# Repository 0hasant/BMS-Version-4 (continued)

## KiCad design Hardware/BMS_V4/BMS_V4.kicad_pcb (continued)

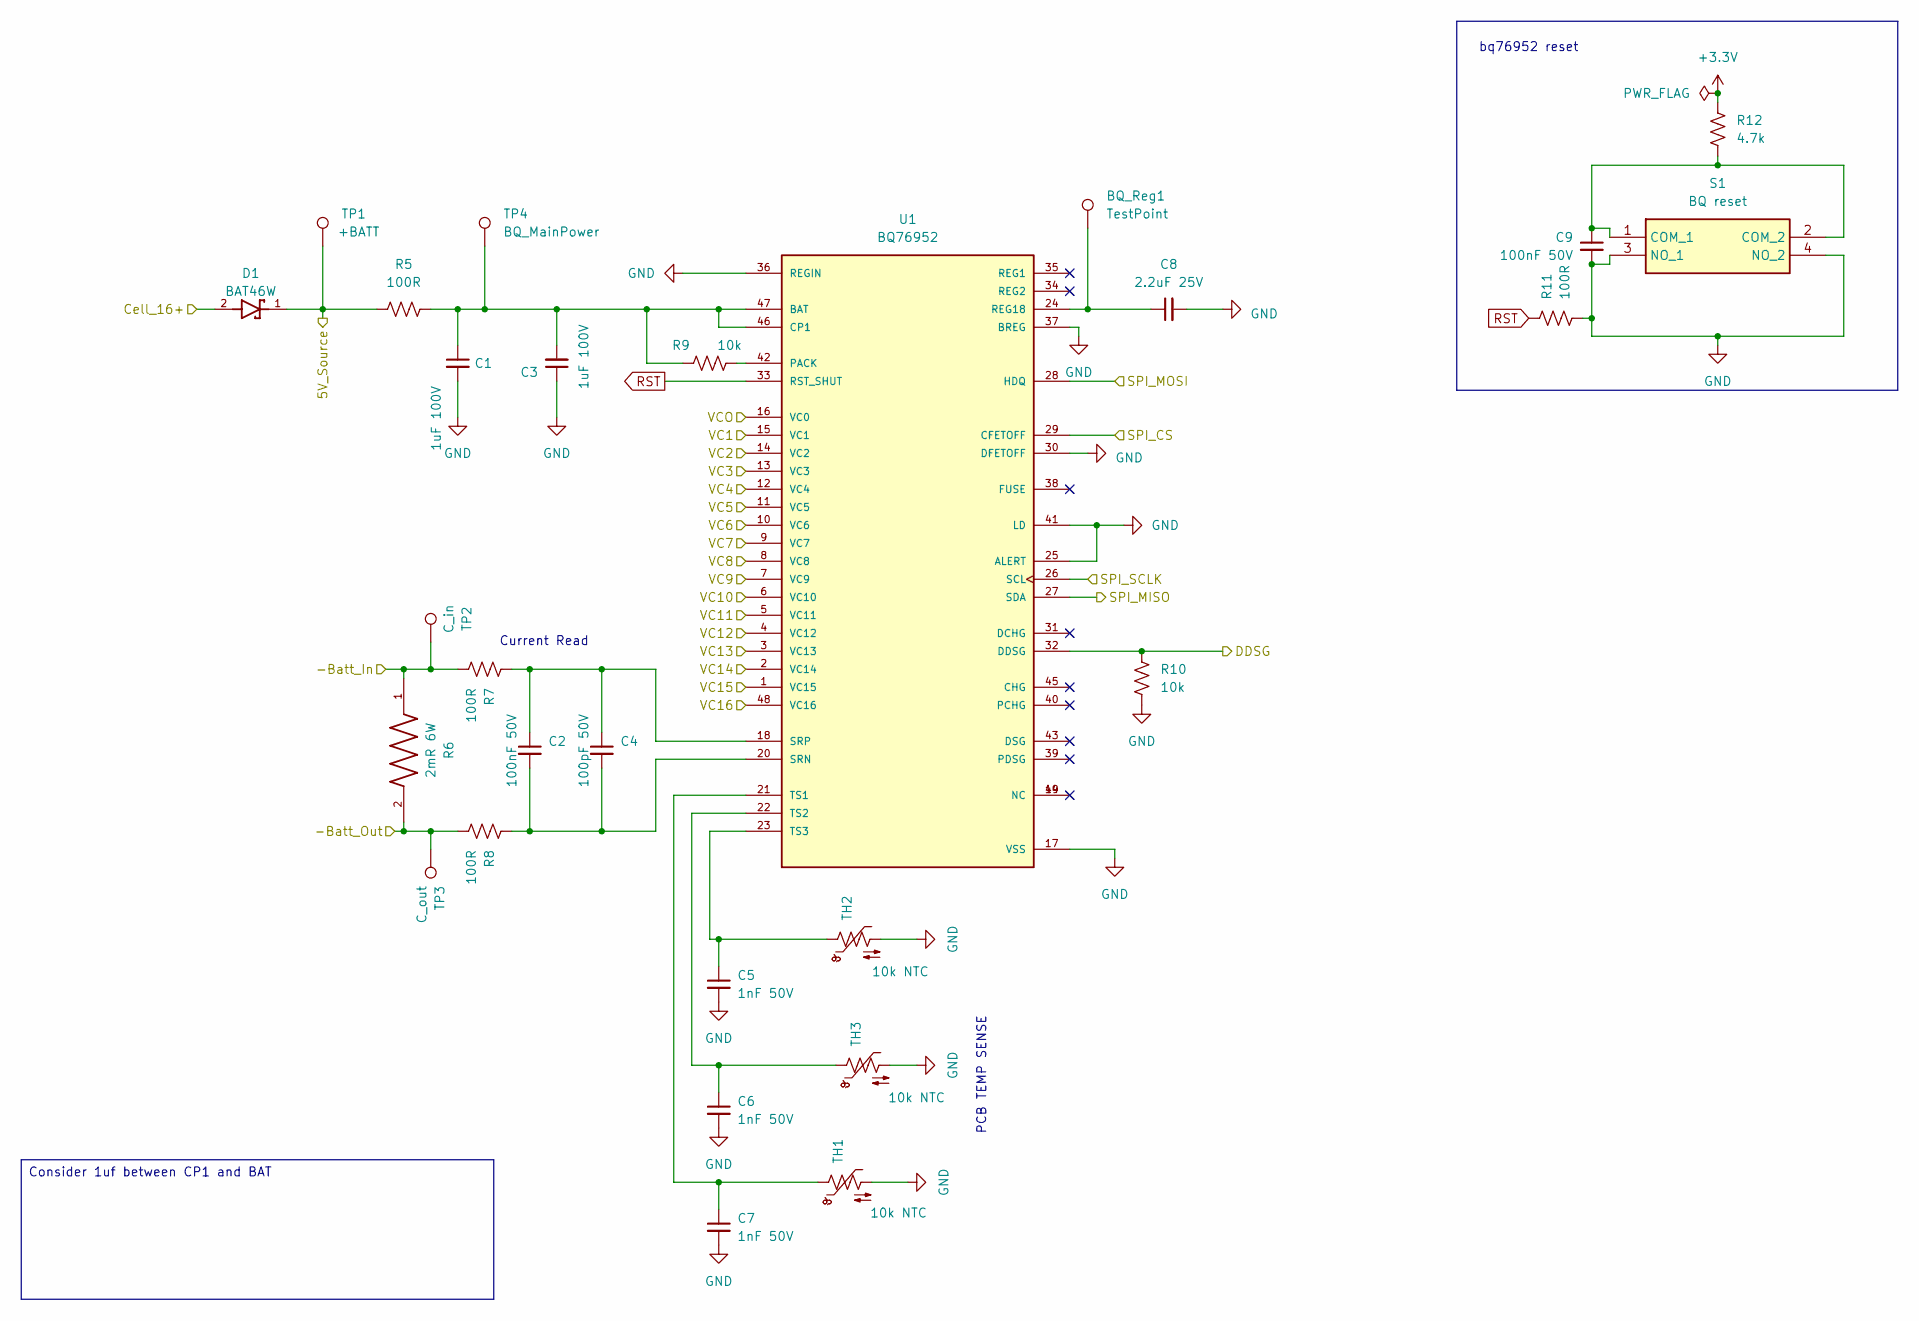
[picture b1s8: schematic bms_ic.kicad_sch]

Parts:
BQ_Reg1: TestPoint; Pin_D0.7mm_L6.5mm_W1.8mm_FlatFork
C1: 1uF 100V; C_1206_3216Metric_Pad1.33x1.80mm_HandSolder; MPN CL31B105KCHNNNE
C2, C9: 100nF 50V; C_0805_2012Metric_Pad1.18x1.45mm_HandSolder; MPN CL21B104KBCNNNC
C3: 1uF 100V; C_0805_2012Metric_Pad1.18x1.45mm_HandSolder; MPN CL21Y105KCFVPJE
C4: 100pF 50V; C_0805_2012Metric_Pad1.18x1.45mm_HandSolder; MPN CL21C101JBANNNC
C5, C6, C7: 1nF 50V; C_0805_2012Metric_Pad1.18x1.45mm_HandSolder; MPN MCF05KTB500102
C8: 2.2uF 25V; C_0805_2012Metric_Pad1.18x1.45mm_HandSolder; MPN CL21B225KAFNNNE
D1: BAT46W; SOD3715X145N; MPN BAT46W-7-F
R5, R11: 100R; R_0805_2012Metric_Pad1.20x1.40mm_HandSolder; MPN 0805S8F1000T5E
R6: 2mR 6W; RESC10052X125N; MPN BVS-A-R002-1.0
R7, R8: 100R; RES_ERA6AHD330V; MPN 0805S8F1000T5E
R9, R10: 10k; R_0805_2012Metric_Pad1.20x1.40mm_HandSolder; MPN 0805S8J0103T5E
R12: 4.7k; R_0805_2012Metric_Pad1.20x1.40mm_HandSolder; MPN CRT05F7E4701
S1: BQ reset; DTS62RV; MPN DTS-62R-V; Mouser Part Number 113-DTS62RV
TH1, TH2, TH3: 10k NTC; R_0805_2012Metric_Pad1.20x1.40mm_HandSolder; MPN TSM2A103F3951RZ
TP1: +BATT; TestPoint_THTPad_D1.0mm_Drill0.5mm
TP2: C_in; TestPoint_THTPad_D1.0mm_Drill0.5mm
TP3: C_out; TestPoint_THTPad_D1.0mm_Drill0.5mm
TP4: BQ_MainPower; TestPoint_THTPad_D1.0mm_Drill0.5mm
U1: BQ76952; QFP50P900X900X120-48N; MPN BQ76952PFBR

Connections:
+3.3V: R12.1; also elsewhere on the board
/Additional Circuits/Cont_PhotoMOS_Anode: R10.2, U1.32 (DDSG); also elsewhere on the board
/BMS_IC/5V_Source: D1.1, R5.1, TP1.1 (1_1); also elsewhere on the board
/BMS_IC/-Batt_In: R6.1, R7.2, TP2.1 (1_1); also elsewhere on the board
/BMS_IC/-Batt_Out: R6.2, R8.2, TP3.1 (1_1); also elsewhere on the board
/BMS_IC/SPI_CS: U1.29 (CFETOFF); also elsewhere on the board
/BMS_IC/SPI_MISO: U1.27 (SDA); also elsewhere on the board
/BMS_IC/SPI_MOSI: U1.28 (HDQ); also elsewhere on the board
/BMS_IC/SPI_SCLK: U1.26 (SCL); also elsewhere on the board
/BMS_IC/VC1: U1.15 (VC1); also elsewhere on the board
/BMS_IC/VC2: U1.14 (VC2); also elsewhere on the board
/BMS_IC/VC3: U1.13 (VC3); also elsewhere on the board
/BMS_IC/VC4: U1.12 (VC4); also elsewhere on the board
/BMS_IC/VC5: U1.11 (VC5); also elsewhere on the board
/BMS_IC/VC6: U1.10 (VC6); also elsewhere on the board
/BMS_IC/VC7: U1.9 (VC7); also elsewhere on the board
/BMS_IC/VC8: U1.8 (VC8); also elsewhere on the board
/BMS_IC/VC9: U1.7 (VC9); also elsewhere on the board
/BMS_IC/VC10: U1.6 (VC10); also elsewhere on the board
/BMS_IC/VC11: U1.5 (VC11); also elsewhere on the board
/BMS_IC/VC12: U1.4 (VC12); also elsewhere on the board
/BMS_IC/VC13: U1.3 (VC13); also elsewhere on the board
/BMS_IC/VC14: U1.2 (VC14); also elsewhere on the board
/BMS_IC/VC15: U1.1 (VC15); also elsewhere on the board
/BMS_IC/VC16: U1.48 (VC16); also elsewhere on the board
/BMS_IC/VCO: U1.16 (VC0); also elsewhere on the board
Cell16+: D1.2; also elsewhere on the board
GND: C1.2, C3.1, C5.2, C6.2, C7.2, C8.2, C9.2, R10.1, R11.1, S1.3 (NO_1), S1.4 (NO_2), TH1.2, TH2.2, TH3.2, U1.17 (VSS), U1.25 (ALERT), U1.30 (DFETOFF), U1.36 (REGIN), U1.37 (BREG), U1.41 (LD); also elsewhere on the board
unnamed: C9.1, R12.2, S1.1 (COM_1), S1.2 (COM_2)
unnamed: C1.1, C3.2, R5.2, R9.1, TP4.1 (1_1), U1.46 (CP1), U1.47 (BAT)
unnamed: R9.2, U1.42 (PACK)
unnamed 156: BQ_Reg1.1, C8.1, U1.24 (REG18); also elsewhere on the board
unnamed: C2.2, C4.2, R8.1, U1.20 (SRN)
unnamed: C2.1, C4.1, R7.1, U1.18 (SRP)
unnamed: C7.1, TH1.1, U1.21 (TS1)
unnamed: C6.1, TH3.1, U1.22 (TS2)
unnamed: C5.1, TH2.1, U1.23 (TS3)
RST: R11.2, U1.33 (RST_SHUT)

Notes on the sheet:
Current Read
PCB TEMP SENSE
bq76952 reset
Consider 1uf between CP1 and BAT

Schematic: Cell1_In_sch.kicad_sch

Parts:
C40, C41: 220nF 50V; C_0805_2012Metric; MPN CL21B224KBFNNNE
D6: BZX584C4V7; D_SOD-523; MPN BZX584C4V7_R2_00001
D7: LED red; LED_0805_2012Metric_Pad1.15x1.40mm_HandSolder; MPN HL-PSC-2012S9AC
Q2: SI1050X; SOTFL50P160X60-6N; MPN SI1050X-T1-GE3
R39: 1k; R_0805_2012Metric_Pad1.20x1.40mm_HandSolder; MPN 0805S8F1001T5E
R40, R41: 100R; R_0805_2012Metric_Pad1.20x1.40mm_HandSolder; MPN CRT05F7E1000
R42: 22R 2W; R_2512_6332Metric_Pad1.40x3.35mm_HandSolder; MPN HP122WJ0220T4E
R43: 0R; R_0805_2012Metric_Pad1.20x1.40mm_HandSolder; MPN 0805S8F0000TDE
R44: 470R; R_0805_2012Metric_Pad1.20x1.40mm_HandSolder; MPN 0805S8F4700T5E
TP10: GND_Test; TestPoint_THTPad_1.5x1.5mm_Drill0.7mm

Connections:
/BMS_IC/VC1: C40.1, R41.1; also elsewhere on the board
/BMS_IC/VCO: C41.1, R39.1, R40.1; also elsewhere on the board
/CellBalance_Input/Cell0: D6.2 (A), Q2.4 (S), R40.2, R43.1; also elsewhere on the board
/CellBalance_Input/Cell1: D7.2 (A), R41.2, R42.1; also elsewhere on the board
GND: C40.2, C41.2, R43.2, TP10.1; also elsewhere on the board
unnamed: D6.1 (K), Q2.3 (G), R39.2
unnamed: D7.1 (K), R44.1
unnamed: Q2.1 (D), Q2.2 (D), Q2.5 (D), Q2.6 (D), R42.2, R44.2

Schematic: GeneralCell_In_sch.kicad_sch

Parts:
C39: 220nF 50V; C_0805_2012Metric; MPN CL21B224KBFNNNE
D4: BZX584C4V7; D_SOD-523; MPN BZX584C4V7_R2_00001
D5: LED red; LED_0805_2012Metric_Pad1.15x1.40mm_HandSolder; MPN HL-PSC-2012S9AC
Q1: SI1050X; SOTFL50P160X60-6N; MPN SI1050X-T1-GE3
R35: 100R; R_0805_2012Metric_Pad1.20x1.40mm_HandSolder; MPN CRT05F7E1000
R36: 1k; R_0805_2012Metric_Pad1.20x1.40mm_HandSolder; MPN 0805S8F1001T5E
R37: 22R 2W; R_2512_6332Metric_Pad1.40x3.35mm_HandSolder; MPN HP122WJ0220T4E
R38: 470R; R_0805_2012Metric_Pad1.20x1.40mm_HandSolder; MPN 0805S8F4700T5E

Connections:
/BMS_IC/VC1: C39.2, R36.1; also elsewhere on the board
/BMS_IC/VC2: C39.1, R35.1; also elsewhere on the board
/CellBalance_Input/Cell1: D4.2 (A), Q1.4 (S); also elsewhere on the board
/CellBalance_Input/Cell2: D5.2 (A), R35.2, R37.1; also elsewhere on the board
unnamed: D4.1 (K), Q1.3 (G), R36.2
unnamed: D5.1 (K), R38.1
unnamed: Q1.1 (D), Q1.2 (D), Q1.5 (D), Q1.6 (D), R37.2, R38.2

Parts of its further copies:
C42, C43, C44, C45, C46, C47, C48, C49, C50, C51, C52, C53, C54: 220nF 50V; C_0805_2012Metric; MPN CL21B224KBFNNNE
D8, D10, D12, D14, D16, D18, D20, D22, D24, D26, D28, D30, D32: BZX584C4V7; D_SOD-523; MPN BZX584C4V7_R2_00001
D9, D11, D13, D15, D17, D19, D21, D23, D25, D27, D29, D31, D33: LED red; LED_0805_2012Metric_Pad1.15x1.40mm_HandSolder; MPN HL-PSC-2012S9AC
Q3, Q4, Q5, Q6, Q7, Q8, Q9, Q10, Q11, Q12, Q13, Q14, Q15: SI1050X; SOTFL50P160X60-6N; MPN SI1050X-T1-GE3
R45, R49, R53, R57, R61, R65, R69, R73, R77, R81, R85, R89, R93: 100R; R_0805_2012Metric_Pad1.20x1.40mm_HandSolder; MPN CRT05F7E1000
R46, R50, R54, R58, R62, R66, R70, R74, R78, R82, R86, R90, R94: 1k; R_0805_2012Metric_Pad1.20x1.40mm_HandSolder; MPN 0805S8F1001T5E
R47, R51, R55, R59, R63, R67, R71, R75, R79, R83, R87, R91, R95: 22R 2W; R_2512_6332Metric_Pad1.40x3.35mm_HandSolder; MPN HP122WJ0220T4E
R48, R52, R56, R60, R64, R68, R72, R76, R80, R84, R88, R92, R96: 470R; R_0805_2012Metric_Pad1.20x1.40mm_HandSolder; MPN 0805S8F4700T5E

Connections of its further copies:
/BMS_IC/VC2: C42.2, R46.1; also elsewhere on the board
/BMS_IC/VC3: C42.1, C43.2, R45.1, R50.1; also elsewhere on the board
/BMS_IC/VC4: C43.1, C44.2, R49.1, R54.1; also elsewhere on the board
/BMS_IC/VC5: C44.1, C45.2, R53.1, R58.1; also elsewhere on the board
/BMS_IC/VC6: C45.1, C46.2, R57.1, R62.1; also elsewhere on the board
/BMS_IC/VC7: C46.1, C47.2, R61.1, R66.1; also elsewhere on the board
/BMS_IC/VC8: C47.1, C48.2, R65.1, R70.1; also elsewhere on the board
/BMS_IC/VC9: C48.1, C49.2, R69.1, R74.1; also elsewhere on the board
/BMS_IC/VC10: C49.1, C50.2, R73.1, R78.1; also elsewhere on the board
/BMS_IC/VC11: C50.1, C51.2, R77.1, R82.1; also elsewhere on the board
/BMS_IC/VC12: C51.1, C52.2, R81.1, R86.1; also elsewhere on the board
/BMS_IC/VC13: C52.1, C53.2, R85.1, R90.1; also elsewhere on the board
/BMS_IC/VC14: C53.1, C54.2, R89.1, R94.1; also elsewhere on the board
/BMS_IC/VC15: C54.1, R93.1; also elsewhere on the board
/CellBalance_Input/Cell2: D8.2 (A), Q3.4 (S); also elsewhere on the board
/CellBalance_Input/Cell3: D9.2 (A), D10.2 (A), Q4.4 (S), R45.2, R47.1; also elsewhere on the board
/CellBalance_Input/Cell4: D11.2 (A), D12.2 (A), Q5.4 (S), R49.2, R51.1; also elsewhere on the board
/CellBalance_Input/Cell5: D13.2 (A), D14.2 (A), Q6.4 (S), R53.2, R55.1; also elsewhere on the board
/CellBalance_Input/Cell6: D15.2 (A), D16.2 (A), Q7.4 (S), R57.2, R59.1; also elsewhere on the board
/CellBalance_Input/Cell7: D17.2 (A), D18.2 (A), Q8.4 (S), R61.2, R63.1; also elsewhere on the board
/CellBalance_Input/Cell8: D19.2 (A), D20.2 (A), Q9.4 (S), R65.2, R67.1; also elsewhere on the board
/CellBalance_Input/Cell9: D21.2 (A), D22.2 (A), Q10.4 (S), R69.2, R71.1; also elsewhere on the board
/CellBalance_Input/Cell10: D23.2 (A), D24.2 (A), Q11.4 (S), R73.2, R75.1; also elsewhere on the board
/CellBalance_Input/Cell11: D25.2 (A), D26.2 (A), Q12.4 (S), R77.2, R79.1; also elsewhere on the board
/CellBalance_Input/Cell12: D27.2 (A), D28.2 (A), Q13.4 (S), R81.2, R83.1; also elsewhere on the board
/CellBalance_Input/Cell13: D29.2 (A), D30.2 (A), Q14.4 (S), R85.2, R87.1; also elsewhere on the board
/CellBalance_Input/Cell14: D31.2 (A), D32.2 (A), Q15.4 (S), R89.2, R91.1; also elsewhere on the board
/CellBalance_Input/Cell15: D33.2 (A), R93.2, R95.1; also elsewhere on the board
unnamed: D8.1 (K), Q3.3 (G), R46.2
unnamed: D9.1 (K), R48.1
unnamed: D10.1 (K), Q4.3 (G), R50.2
unnamed: D11.1 (K), R52.1
unnamed: D12.1 (K), Q5.3 (G), R54.2
unnamed: D13.1 (K), R56.1
unnamed: D14.1 (K), Q6.3 (G), R58.2
unnamed: D15.1 (K), R60.1
unnamed: D16.1 (K), Q7.3 (G), R62.2
unnamed: D17.1 (K), R64.1
unnamed: D18.1 (K), Q8.3 (G), R66.2
unnamed: D19.1 (K), R68.1
unnamed: D20.1 (K), Q9.3 (G), R70.2
unnamed: D21.1 (K), R72.1
unnamed: D22.1 (K), Q10.3 (G), R74.2
unnamed: D23.1 (K), R76.1
unnamed: D24.1 (K), Q11.3 (G), R78.2
unnamed: D25.1 (K), R80.1
unnamed: D26.1 (K), Q12.3 (G), R82.2
unnamed: D27.1 (K), R84.1
unnamed: D28.1 (K), Q13.3 (G), R86.2
unnamed: D29.1 (K), R88.1
unnamed: D30.1 (K), Q14.3 (G), R90.2
unnamed: D31.1 (K), R92.1
unnamed: D32.1 (K), Q15.3 (G), R94.2
unnamed: D33.1 (K), R96.1
unnamed: Q3.1 (D), Q3.2 (D), Q3.5 (D), Q3.6 (D), R47.2, R48.2
unnamed: Q4.1 (D), Q4.2 (D), Q4.5 (D), Q4.6 (D), R51.2, R52.2
unnamed: Q5.1 (D), Q5.2 (D), Q5.5 (D), Q5.6 (D), R55.2, R56.2
unnamed: Q6.1 (D), Q6.2 (D), Q6.5 (D), Q6.6 (D), R59.2, R60.2
unnamed: Q7.1 (D), Q7.2 (D), Q7.5 (D), Q7.6 (D), R63.2, R64.2
unnamed: Q8.1 (D), Q8.2 (D), Q8.5 (D), Q8.6 (D), R67.2, R68.2
unnamed: Q9.1 (D), Q9.2 (D), Q9.5 (D), Q9.6 (D), R71.2, R72.2
unnamed: Q10.1 (D), Q10.2 (D), Q10.5 (D), Q10.6 (D), R75.2, R76.2
unnamed: Q11.1 (D), Q11.2 (D), Q11.5 (D), Q11.6 (D), R79.2, R80.2
unnamed: Q12.1 (D), Q12.2 (D), Q12.5 (D), Q12.6 (D), R83.2, R84.2
unnamed: Q13.1 (D), Q13.2 (D), Q13.5 (D), Q13.6 (D), R87.2, R88.2
unnamed: Q14.1 (D), Q14.2 (D), Q14.5 (D), Q14.6 (D), R91.2, R92.2
unnamed: Q15.1 (D), Q15.2 (D), Q15.5 (D), Q15.6 (D), R95.2, R96.2

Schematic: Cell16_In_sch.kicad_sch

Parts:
C55: 220nF 50V; C_0805_2012Metric; MPN CL21B224KBFNNNE
D34: BZX584C4V7; D_SOD-523; MPN BZX584C4V7_R2_00001
D35: LED red; LED_0805_2012Metric_Pad1.15x1.40mm_HandSolder; MPN HL-PSC-2012S9AC
Q16: SI1050X; SOTFL50P160X60-6N; MPN SI1050X-T1-GE3
R97: 20R; RESC2012X70N; MPN 0805S8F200JT5E
R98: 1k; R_0805_2012Metric_Pad1.20x1.40mm_HandSolder; MPN 0805S8F1001T5E
R99: 22R 2W; R_2512_6332Metric_Pad1.40x3.35mm_HandSolder; MPN HP122WJ0220T4E
R100: 470R; R_0805_2012Metric_Pad1.20x1.40mm_HandSolder; MPN 0805S8F4700T5E

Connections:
/BMS_IC/VC15: C55.2, R98.1; also elsewhere on the board
/BMS_IC/VC16: C55.1, R97.1; also elsewhere on the board
/CellBalance_Input/Cell15: D34.2 (A), Q16.4 (S); also elsewhere on the board
Cell16+: D35.2 (A), R97.2, R99.1; also elsewhere on the board
unnamed: D34.1 (K), Q16.3 (G), R98.2
unnamed: D35.1 (K), R100.1
unnamed: Q16.1 (D), Q16.2 (D), Q16.5 (D), Q16.6 (D), R99.2, R100.2

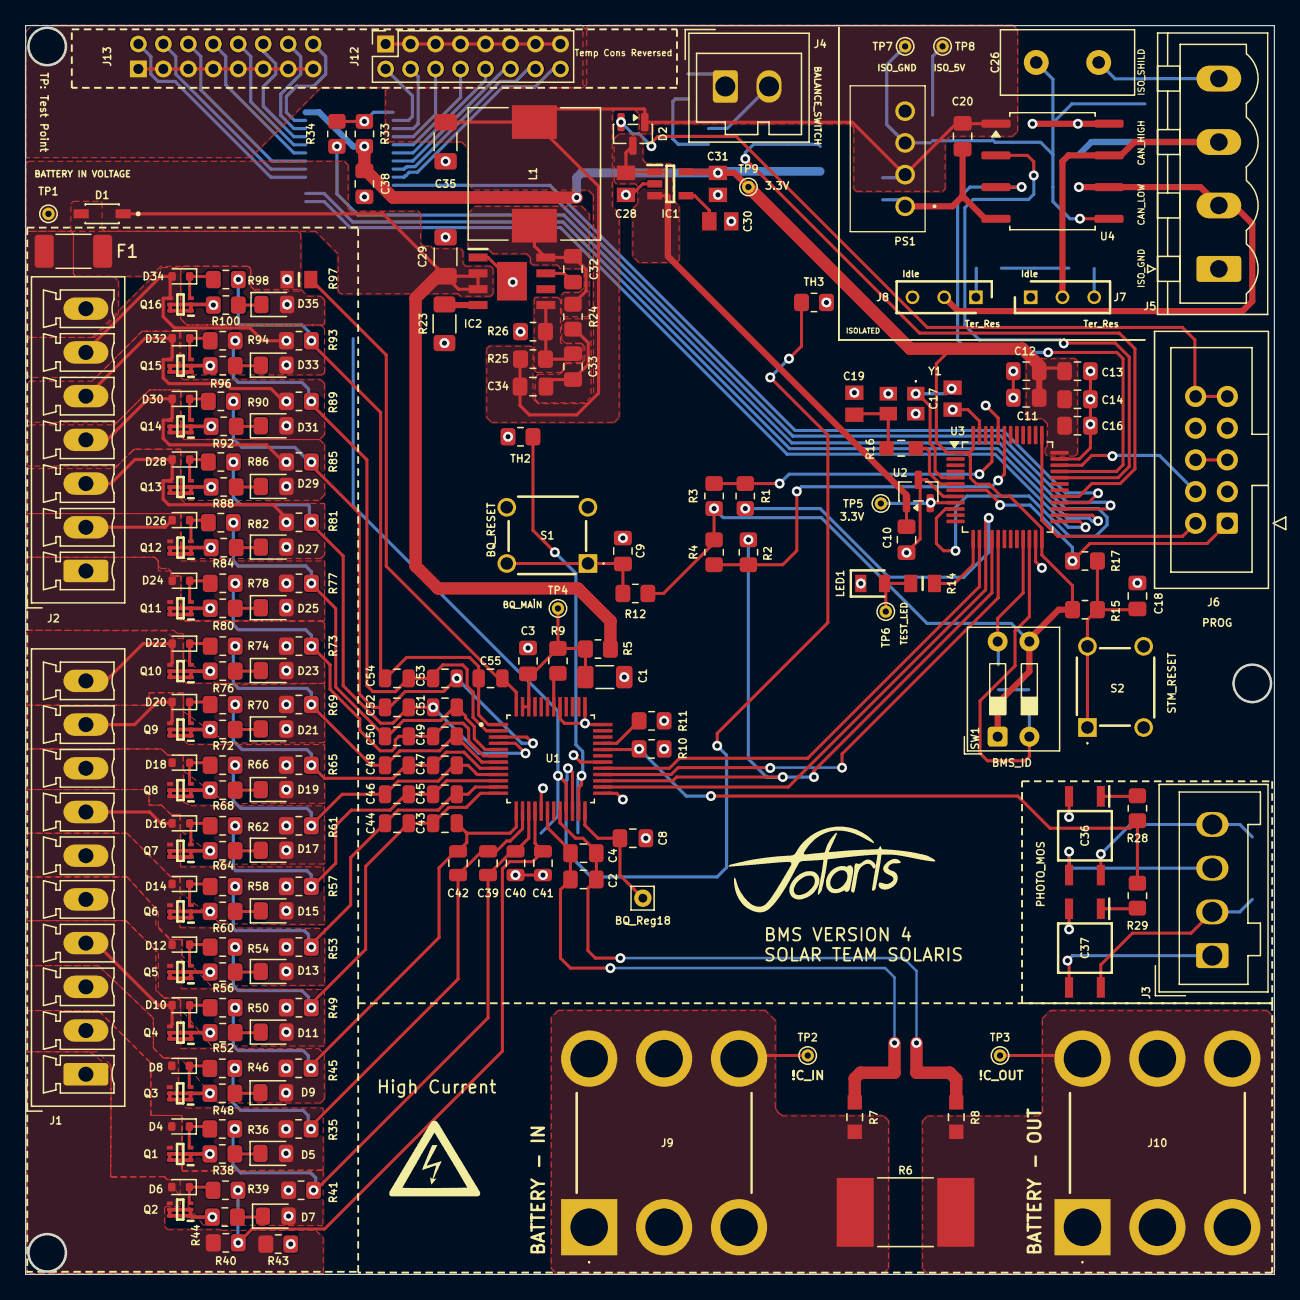
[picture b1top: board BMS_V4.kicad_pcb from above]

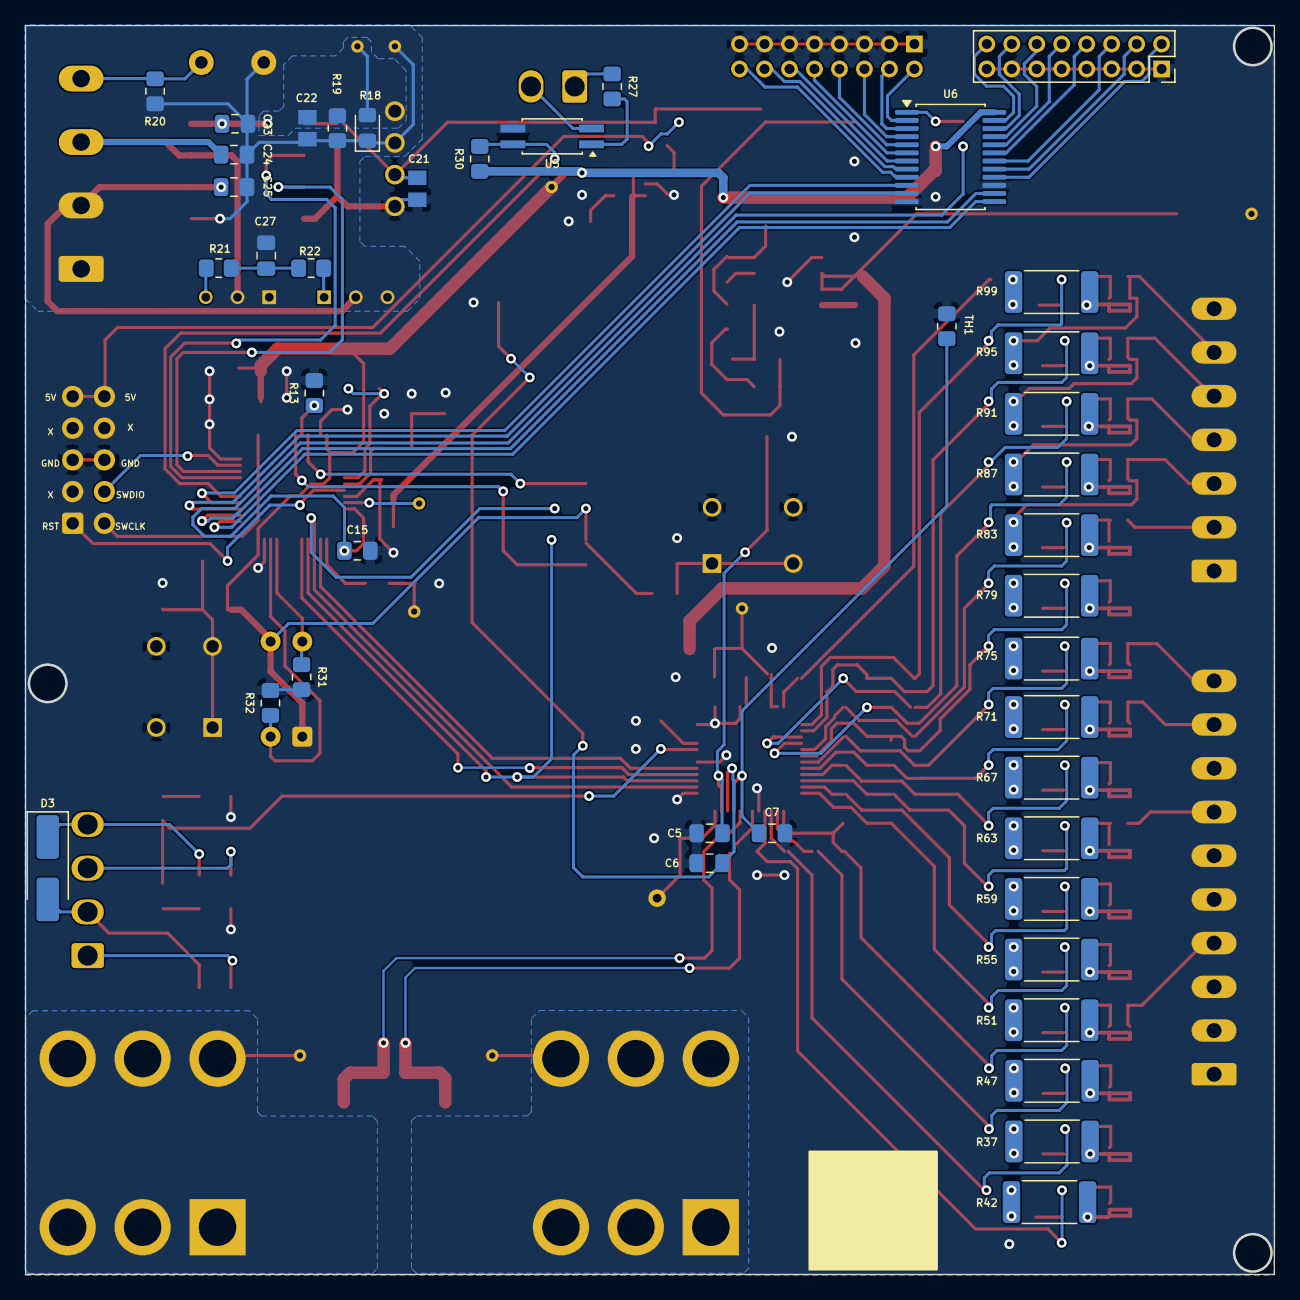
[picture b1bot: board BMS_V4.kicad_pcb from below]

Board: 2 copper layers, 100.0 x 100.0 mm, 247 parts (41 on the bottom side), 169 nets.

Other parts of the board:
BQ_Reg18: TestPoint; Pin_D0.7mm_L6.5mm_W1.8mm_FlatFork
TP9: +3.3V; TestPoint_THTPad_D1.0mm_Drill0.5mm

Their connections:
+3.3V: TP9.1 (1_1); also elsewhere on the board
unnamed 156: BQ_Reg18.1 (1_1); also elsewhere on the board

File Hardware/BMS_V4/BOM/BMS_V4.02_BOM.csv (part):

References,Qty per board,Value,Description,Footprint,Manufacturer,MPN,Ozdisan link,Ozdisan stock 2026-10-13,Unit price TRY at MOQ,MOQ,Fitted,Notes
C1,1,1uF 100V,MLCC 1206 1uF 100V X7R,C_1206_3216Metric_Pad1.33x1.80mm_HandSolder,Samsung,CL31B105KCHNNNE,https://www.ozdisan.com/en/p/smt-smd-and-mlcc-capacitors-184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,0,3.22577,2,yes,BAT pin. Not stocked: the 0805 CL21Y105KCFVPJE (in stock) can be hand-soldered on these 1206 pads
"C2, C9, C12, C13, C14, C16, C18, C20, C23, C38",10,100nF 50V,MLCC 0805 100nF 50V X7R,C_0805_2012Metric_Pad1.18x1.45mm_HandSolder,Samsung,CL21B104KBCNNNC,https://www.ozdisan.com/en/p/smt-smd-and-mlcc-capacitors-184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,65330,0.69204,10,yes,SRP-SRN filter
C3,1,1uF 100V,MLCC 0805 1uF 100V X7S,C_0805_2012Metric_Pad1.18x1.45mm_HandSolder,Samsung,CL21Y105KCFVPJE,https://www.ozdisan.com/en/p/smt-smd-and-mlcc-capacitors-184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,60891,11.8517,1,yes,BAT pin. Was a 1206 part number (CL31B105KCHNNNE) on an 0805 footprint
C4,1,100pF 50V,MLCC 0805 100pF 50V C0G,C_0805_2012Metric_Pad1.18x1.45mm_HandSolder,Samsung,CL21C101JBANNNC,https://www.ozdisan.com/en/p/smt-smd-and-mlcc-capacitors-184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,823356,0.60916,10,yes,SRP-SRN filter
"C5, C6, C7",3,1nF 50V,MLCC 0805 1nF 50V X7R,C_0805_2012Metric_Pad1.18x1.45mm_HandSolder,Viking,MCF05KTB500102,https://www.ozdisan.com/en/p/smt-smd-and-mlcc-capacitors-184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,16113,0.69990,10,yes,Thermistor filter
C8,1,2.2uF 25V,MLCC 0805 2.2uF 25V X7R,C_0805_2012Metric_Pad1.18x1.45mm_HandSolder,Samsung,CL21B225KAFNNNE,https://www.ozdisan.com/en/p/smt-smd-and-mlcc-capacitors-184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,783799,2.07405,5,yes,REG18
C10,1,470nF 50V,MLCC 0805 470nF 50V X7R,C_0805_2012Metric_Pad1.18x1.45mm_HandSolder,Samsung,CL21B474KBFNNNE,https://www.ozdisan.com/en/p/smt-smd-and-mlcc-capacitors-184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,20455,0.96737,10,yes,
"C11, C22",2,10uF 25V,MLCC 0805 10uF 25V X7S,C_0805_2012Metric_Pad1.18x1.45mm_HandSolder,Murata,GRT21BC71E106KE13L,https://www.ozdisan.com/en/p/smt-smd-and-mlcc-capacitors-184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,396,24.8136,1,yes,Samsung CL21A106KAYNNNE is cheaper but not stocked
"C15, C30",2,10nF 50V,MLCC 0805 10nF 50V X7R,C_0805_2012Metric_Pad1.18x1.45mm_HandSolder,Samsung,CL21B103KBANNNC,https://www.ozdisan.com/en/p/smt-smd-and-mlcc-capacitors-184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,587532,0.79501,10,yes,
"C17, C19",2,22pF 50V,MLCC 0805 22pF 50V C0G,CAPC2012X94N,Samsung,CL21C220JBANNNC,https://www.ozdisan.com/en/p/smt-smd-and-mlcc-capacitors-184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,2614482,0.59880,10,yes,Crystal load
C21,1,4.7uF 25V,MLCC 0805 4.7uF 25V X5R,CAPC2012X94N,Samsung,CL21A475KAQNNNE,https://www.ozdisan.com/en/p/smt-smd-and-mlcc-capacitors-184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,4706,1.38365,5,yes,
"C24, C25",2,30pF 50V,MLCC 0805 30pF 50V C0G,C_0805_2012Metric_Pad1.18x1.45mm_HandSolder,Samsung,CL21C300JBANNNC,https://www.ozdisan.com/en/p/smt-smd-and-mlcc-capacitors-184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,0,,10,yes,CAN_H/CAN_L filter. Not stocked (33pF neither); 47pF CL21C470JBANNNC is in stock if you accept the change
C26,1,3.3nF 2kV,"Ceramic disc 3.3nF 2kV, 5 mm pitch",C_Disc_D10.5mm_W5.0mm_P5.00mm,Cinetech,KB3D332KL518Y,https://www.ozdisan.com/en/p/ceramic-capacitors-181/cinetech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,0,12.9453,1,yes,"CAN shield to ISO_GND. Not stocked: any 3.3nF >= 1kV disc, 5 mm pitch"
C27,1,10pF 50V,MLCC 0805 10pF 50V C0G,C_0805_2012Metric_Pad1.18x1.45mm_HandSolder,Yageo,CC0805JRNPO9BN100,https://www.ozdisan.com/en/p/smt-smd-and-mlcc-capacitors-184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,90147,0.88139,10,yes,CAN split termination: 4.7nF recommended (see README)
"C28, C31",2,1uF 50V,MLCC 0805 1uF 50V X7R,CAPC2012X94N,Samsung,CL21B105KBFNNNE,https://www.ozdisan.com/en/p/smt-smd-and-mlcc-capacitors-184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,5273,1.66545,5,yes,
C29,1,2.2uF 100V,MLCC 1206 2.2uF 100V X7R,C_1206_3216Metric_Pad1.33x1.80mm_HandSolder,Samsung,CL31B225KCHSNNE,https://www.ozdisan.com/en/p/smt-smd-and-mlcc-capacitors-184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,0,11.8159,1,yes,LM5163 input. Not stocked (TDK/Murata/Yageo 1206 2.2uF 100V neither): request
"C32, C34",2,2.2nF 50V,MLCC 0805 2.2nF 50V X7R,C_0805_2012Metric_Pad1.18x1.45mm_HandSolder,Viking,MCF05KTB500222,https://www.ozdisan.com/en/p/smt-smd-and-mlcc-capacitors-184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,171079,0.32833,20,yes,LM5163 BST / ripple
C33,1,56pF 50V,MLCC 0805 56pF 50V C0G,C_0805_2012Metric_Pad1.18x1.45mm_HandSolder,Viking,MCF05JTN500560,https://www.ozdisan.com/en/p/smt-smd-and-mlcc-capacitors-184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,0,0.32833,20,yes,LM5163 ripple injection. Not stocked (Samsung/Yageo 56pF neither): request
C35,1,10uF 50V,MLCC 1206 10uF 50V X5R,C_1206_3216Metric_Pad1.33x1.80mm_HandSolder,TDK,CGA5L3X5R1H106M160AB,https://www.ozdisan.com/en/p/smt-smd-and-mlcc-capacitors-184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,9,59.2218,1,yes,LM5163 output. Samsung CL31B106KBHNNNE not stocked
"C36, C37",2,AQY212GS,"PhotoMOS relay 60V 1A, SOP4",SOP254P680X230-4N,Panasonic,AQY212GSZ,https://www.ozdisan.com/en/p/solid-state-relays-405/panasoni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,21596,61.2682,1,yes,Contactor high/low side. Reference should be K1/K2
"C39, C40, C41, C42, C43, C44, C45, C46, C47, C48, C49, C50, C51, C52, C53, C54, C55",17,220nF 50V,MLCC 0805 220nF 50V X7R,C_0805_2012Metric,Samsung,CL21B224KBFNNNE,https://www.ozdisan.com/en/p/smt-smd-and-mlcc-capacitors-184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,8200,0.72212,10,yes,"Cell filter. Was 200nF: not stocked, 220nF is the nearest standard value"
D1,1,BAT46W,"Schottky 100V 150mA, SOD-123",SOD3715X145N,Diodes Inc.,BAT46W-7-F,https://www.ozdisan.com/en/p/schottky-diodes-385/diodes-bat4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,0,3.15372,2,yes,BAT supply. Not stocked (Vishay BAT46W-E3-08 neither): request
D2,1,BAT54C,"Dual Schottky common cathode 30V 200mA, SOT-23",SOT-23,onsemi,BAT54CLT1G,https://www.ozdisan.com/en/p/schottky-diodes-385/ons-bat54cl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,5817,1.09266,5,yes,5V OR-ing
D3,1,M7,"Rectifier 1000V 1A, SMA",D_SMA_Handsoldering,Hottech,M7-HT,https://www.ozdisan.com/en/p/rectifier-diodes-389/hottech-m7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,3682437,0.39058,20,yes,Contactor coil flyback
"D4, D6, D8, D10, D12, D14, D16, D18, D20, D22, D24, D26, D28, D30, D32, D34",16,BZX584C4V7,"Zener 4.7V 200mW, SOD-523",D_SOD-523,Panjit,BZX584C4V7_R2_00001,https://www.ozdisan.com/en/p/zener-diodes-390/panjit-bzx584c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,94897,1.68922,5,yes,Balance FET gate clamp
"D5, D7, D9, D11, D13, D15, D17, D19, D21, D23, D25, D27, D29, D31, D33, D35",16,LED red,LED red 0805,LED_0805_2012Metric_Pad1.15x1.40mm_HandSolder,Honglitronic,HL-PSC-2012S9AC,https://www.ozdisan.com/en/p/led-signal-color-361/honglitron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,180352,0.80489,25,yes,Balancing indicator
F1,1,1A slow,"Fuse 1A 125V time-lag, 2410",Fuse_2010_5025Metric_Pad1.52x2.65mm_HandSolder,Reomax,SET1100,https://www.ozdisan.com/en/p/fuses-849/reomax-set1100-525709,6894,4.31847,5,yes,Was 250mA (blows when top cell balances). 2410 body on 2010 footprint
IC1,1,TPS73233,"LDO 3.3V 250mA, SOT-23-5",SOT95P280X145-5N,Texas Instruments,TPS73233DBVR,https://www.ozdisan.com/en/p/linear-voltage-regulators-279/t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,1802,43.4955,1,yes,Reference should be U7
IC2,1,LM5163-Q1,"Buck 100V 0.5A, SO-8 PowerPAD",SOIC127P600X170-9N,Texas Instruments,LM5163HQDDARQ1,https://www.ozdisan.com/en/p/dc-dc-switching-voltage-regulat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,820,168.233,1,yes,Reference should be U8
J1,1,Cells 0-9,"Header 10P 3.5mm vertical, closed","PhoenixContact_MCV_1,5_10-G-3.5_1x10_P3.50mm_Vertical",Degson,15EDGVC-3.5-10P-14-00AH,https://www.ozdisan.com/en/p/pluggable-terminal-blocks-411/d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,848,10.6725,1,yes,Plug: 15EDGK-3.5-10P-14-00AH
J2,1,Cells 10-16+,"Header 7P 3.5mm vertical, closed","PhoenixContact_MCV_1,5_7-G-3.5_1x07_P3.50mm_Vertical",Degson,15EDGVC-3.5-07P-13-00AH,https://www.ozdisan.com/en/p/pluggable-terminal-blocks-411/d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,239,13.5929,1,yes,Plug: 15EDGK-3.5-07P-13-00AH
J3,1,Contactor,"Header 4P 3.5mm vertical, closed",Wago_734-134_1x04_P3.50mm_Vertical,Degson,15EDGVC-3.5-04P-13-00AH,https://www.ozdisan.com/en/p/pluggable-terminal-blocks-411/d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,2384,6.41932,1,yes,Footprint is Wago 734-134: check fit. Plug: 15EDGK-3.5-04P-13-00AH
J4,1,Balance EN,"Header 2P 3.5mm vertical, closed",Wago_734-132_1x02_P3.50mm_Vertical,Degson,15EDGVC-3.5-02P-12-00AH,https://www.ozdisan.com/en/p/pluggable-terminal-blocks-411/d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,2659,3.20966,1,yes,Blue (black not stocked). Footprint is Wago 734-132: check fit
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
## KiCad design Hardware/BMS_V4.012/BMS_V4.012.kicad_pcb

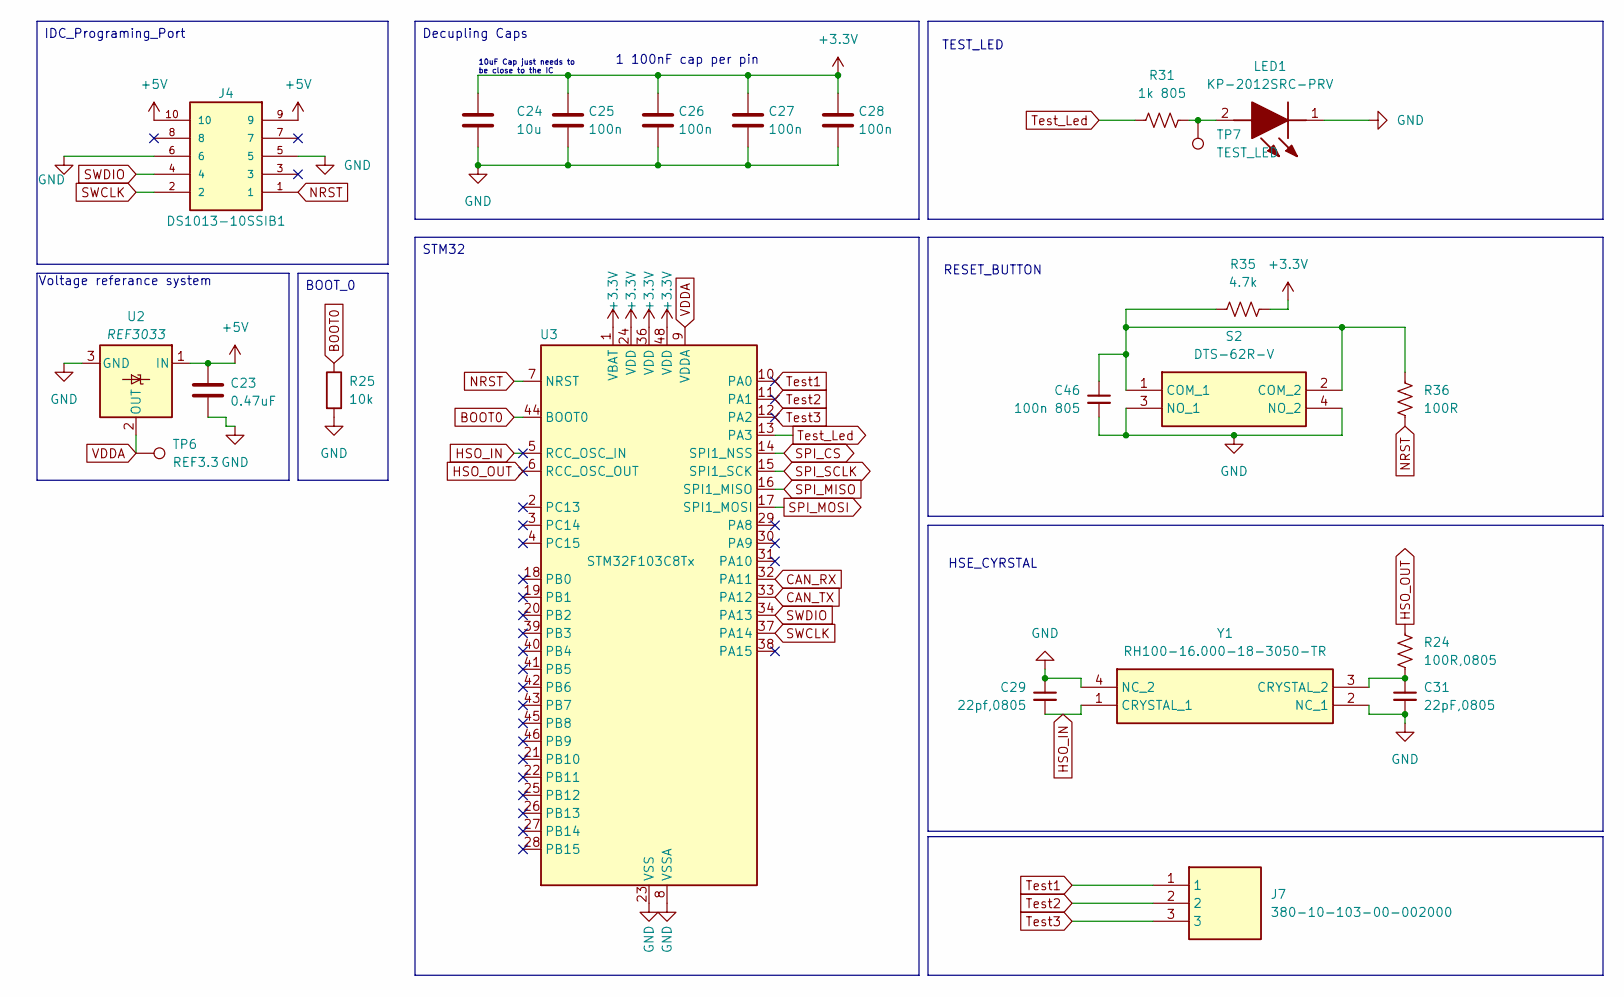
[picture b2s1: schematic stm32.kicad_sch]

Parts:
C23: 0.47uF; C_0805_2012Metric_Pad1.18x1.45mm_HandSolder
C24: 10u; C_0805_2012Metric_Pad1.18x1.45mm_HandSolder
C25, C26, C27, C28: 100n; C_0805_2012Metric_Pad1.18x1.45mm_HandSolder
C29: 22pf,0805; CAPC2012X94N
C31: 22pF,0805; CAPC2012X94N
C46: 100n 805; C_0805_2012Metric_Pad1.18x1.45mm_HandSolder
J4: DS1013-10SSIB1; IDC-Header_2x05_P2.54mm_Vertical; PARTREV G
J7: 380-10-103-00-002000; HDRV3W51P0X254_1X3_762X254X470P; Manufacturer_Part_Number 380-10-103-00-002000; Mouser Part Number 575-3801010300002000
LED1: KP-2012SRC-PRV; LEDC2012X110N; Manufacturer_Part_Number KP-2012SRC-PRV; Mouser Part Number N/A
R24: 100R,0805; RES_ERA6AHD330V
R25: 10k; R_0805_2012Metric_Pad1.20x1.40mm_HandSolder
R31: 1k 805; RESC2012X70N
R35: 4.7k; R_0805_2012Metric_Pad1.20x1.40mm_HandSolder
R36: 100R; R_0805_2012Metric_Pad1.20x1.40mm_HandSolder
S2: DTS-62R-V; DTS62RV; Manufacturer_Part_Number DTS-62R-V; Mouser Part Number 113-DTS62RV
TP6: REF3.3; TestPoint_THTPad_D1.0mm_Drill0.5mm
TP7: TEST_LED; TestPoint_THTPad_D1.0mm_Drill0.5mm
U2: REF3033; SOT-23
U3: STM32F103C8Tx; LQFP-48_7x7mm_P0.5mm
Y1: RH100-16.000-18-3050-TR; RH10016000183050TR; Manufacturer_Part_Number RH100-16.000-18-3050-TR

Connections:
+3.3V: C24.1, C25.1, C26.1, C27.1, C28.1, R35.2, U3.1 (VBAT), U3.24 (VDD), U3.36 (VDD), U3.48 (VDD); also elsewhere on the board
+5V: C23.1, J4.9, J4.10, U2.1 (IN); also elsewhere on the board
BOOT0: R25.1, U3.44 (BOOT0)
CAN_RX: U3.32 (PA11); also elsewhere on the board
CAN_TX: U3.33 (PA12); also elsewhere on the board
GND: C23.2, C24.2, C25.2, C26.2, C27.2, C28.2, C29.1, C31.2, C46.2, J4.5, J4.6, LED1.1 (K), R25.2, S2.3 (NO_1), S2.4 (NO_2), U2.3 (GND), U3.8 (VSSA), U3.23 (VSS), U3.35 (VSS), U3.47 (VSS), Y1.2 (NC_1), Y1.4 (NC_2); also elsewhere on the board
HSO_IN: C29.2, U3.5 (RCC_OSC_IN), Y1.1 (CRYSTAL_1)
HSO_OUT: R24.1, U3.6 (RCC_OSC_OUT)
NRST: J4.1, R36.1, U3.7 (NRST)
unnamed: LED1.2 (A), R31.2, TP7.1
unnamed: C46.1, R35.1, R36.2, S2.1 (COM_1), S2.2 (COM_2)
unnamed: C31.1, R24.2, Y1.3 (CRYSTAL_2)
SPI_CS: U3.14 (SPI1_NSS); also elsewhere on the board
SPI_MISO: U3.16 (SPI1_MISO); also elsewhere on the board
SPI_MOSI: U3.17 (SPI1_MOSI); also elsewhere on the board
SPI_SCLK: U3.15 (SPI1_SCK); also elsewhere on the board
SWCLK: J4.2, U3.37 (PA14)
SWDIO: J4.4, U3.34 (PA13)
Test1: J7.1, U3.10 (PA0)
Test2: J7.2, U3.11 (PA1)
Test3: J7.3, U3.12 (PA2)
Test_Led: R31.1, U3.13 (PA3)
VDDA: TP6.1, U2.2 (OUT), U3.9 (VDDA)

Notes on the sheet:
HSE_CYRSTAL
TEST_LED
1 100nF cap per pin
Voltage referance system
RESET_BUTTON
10uF Cap just needs to be close to the IC
BOOT_0
IDC_Programing_Port
Decupling Caps
STM32
